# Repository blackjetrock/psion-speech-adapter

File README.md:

# psion-speech-adapter
Psion Organiser speech adatper

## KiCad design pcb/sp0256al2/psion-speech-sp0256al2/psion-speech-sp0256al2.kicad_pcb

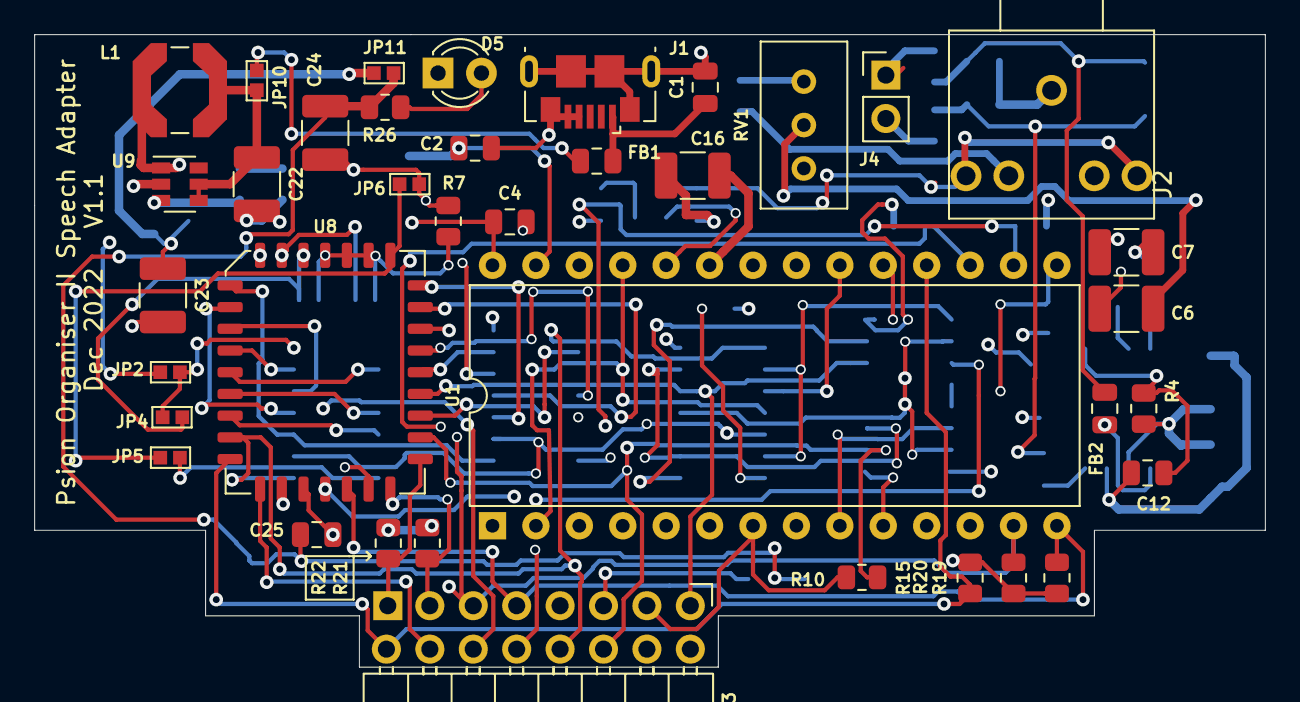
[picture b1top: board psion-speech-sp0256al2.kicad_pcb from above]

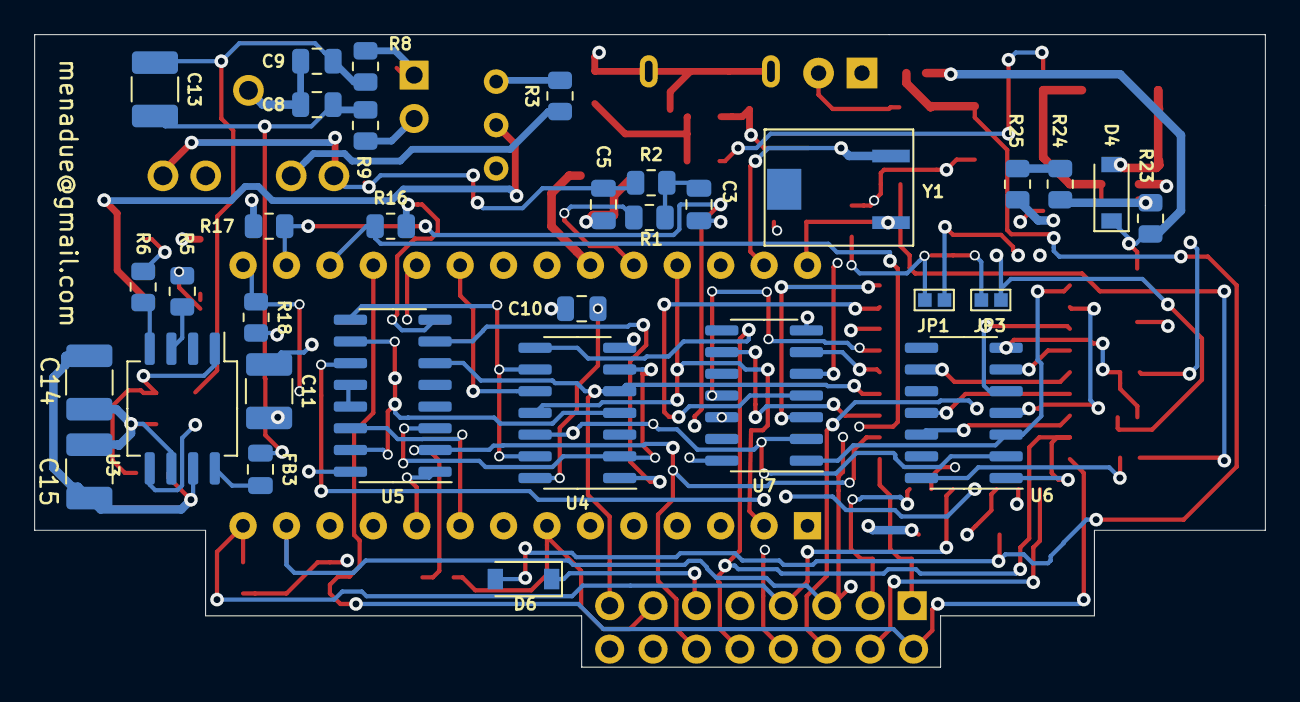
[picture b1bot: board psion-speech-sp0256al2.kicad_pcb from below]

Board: 4 copper layers, 72.0 x 37.0 mm, 71 parts (33 on the bottom side), 68 nets.

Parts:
C1: 10nF; C_0805_2012Metric
C2, C4: 12pF; C_0805_2012Metric
C3, C5: 22nF; C_0805_2012Metric
C6, C7: 1uF; C_1210_3225Metric_Pad1.33x2.70mm_HandSolder
C8, C9: 220pF; C_0805_2012Metric
C10, C12, C25: 100nF; C_0805_2012Metric
C11, C24: 10uF; C_1210_3225Metric_Pad1.33x2.70mm_HandSolder
C13: nopop; C_1210_3225Metric_Pad1.33x2.70mm_HandSolder
C14, C15, C16: 20uF; C_1210_3225Metric_Pad1.33x2.70mm_HandSolder
C22, C23: 22uF; C_1210_3225Metric_Pad1.33x2.70mm_HandSolder
D4, D6: SS36; D_SOD-123
D5: LED; LED_D3.0mm
FB1, FB2, FB3: Laird Technologies Part # MI0805K400R-10; C_0805_2012Metric
J1: Connector_USB_B_Micro; USB_Micro-B_GCT_USB3076-30-A
J2: AudioJack2_Ground_Switch; truconnect_stereo_audio_5_pin
J3: Conn_02x08_Odd_Even; Psion_datapak_2x08_P2.54mm_Horizontal
J4: Conn_01x02_Female; PinHeader_1x02_P2.54mm_Vertical
JP1, JP2, JP3, JP4, JP5, JP6, JP10: Jumper_NO_Small; SolderJumper-2_P1.3mm_Open_Pad0.8x0.8mm
JP11: SolderJumper_2_Open; SolderJumper-2_P1.3mm_Open_Pad0.8x0.8mm
L1: 22uH; L_Coilcraft_LPS5030
R1, R2: 33K; R_0805_2012Metric
R3: 0R; R_0805_2012Metric
R4: 10k; R_0805_2012Metric
R5, R6: 100R; R_0805_2012Metric
R7, R10, R15, R16, R17, R18, R19, R20, R21, R22: 47k; R_0805_2012Metric
R8, R9: R_Small; R_0805_2012Metric
R23: 100k; R_0805_2012Metric
R24: 5k; R_0805_2012Metric
R25: 1k; R_0805_2012Metric
R26: 1k8; R_0805_2012Metric
RV1: 10k; Potentiometer_Bourns_3296W_Vertical
U1: SP0256AL2; DIP-28_W15.24mm
U3: PAM8302AAD; SO-8_5.3x6.2mm_P1.27mm
U4: 4011; SOIC-14_3.9x8.7mm_P1.27mm
U5: 74LS368; SOIC-16_3.9x9.9mm_P1.27mm
U6, U7: 4024; SOIC-14_3.9x8.7mm_P1.27mm
U8: SST39SF020; PLCC-32_11.4x14.0mm_P1.27mm
U9: Regulator_Switching_MT3608; SOT-23-6
Y1: 3.2768MHz; crystal_um4s

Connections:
5VUSB: FB1.1, JP10.1
+10V_PSION: C24.1, C25.1, D6.2, JP11.2, R26.1
A15: JP1.1, JP2.1, U8.3
A16: JP3.1, JP4.1, U8.2
A17: JP5.1, JP6.1, U8.30
ALD: U1.20, U4.10
GND: C1.2, C2.2, C3.2, C4.2, C5.2, C7.2, C8.2, C9.2, C10.2, C11.2, C12.2, C14.2, C15.2, C16.2, C22.2, C23.2, C24.2, C25.2, D5.1, J1.4, J1.5, J1.6, J2.G, J3.9, JP2.2, JP4.2, JP6.2, R7.2, R15.2, R16.2, R17.2, R18.2, R19.2, R20.2, R21.2, R22.2, R25.2, RV1.3, U1.1, U1.10, U1.11, U1.22, U3.7, U4.7, U5.1, U5.8, U6.7, U7.7, U8.16, U9.2
LRQ: U1.9, U5.14
NOT_SEL_SOE_1: U4.9, U4.13, U5.9
N_SOE: U4.1, U5.7
N_SS: U4.2, U4.6, U5.3
unnamed: C1.1, FB1.2, J1.1
unnamed: C2.1, U1.27, Y1.1
unnamed: C3.1, R1.1, R2.2
unnamed: C4.1, U1.28, Y1.2
unnamed: C5.1, J2.S, J2.T, R2.1
unnamed: C6.1, R5.2
unnamed: C6.2, RV1.2
unnamed: C7.1, R6.2
unnamed: C12.1, R4.2, U3.1
unnamed: C9.1, C13.1, FB2.1, R8.2
unnamed: C8.1, C13.2, FB3.1, R9.1
unnamed: C22.1, JP10.2, L1.1, U9.4, U9.5
unnamed: C23.1, D4.1, JP11.1, R23.1
unnamed: D4.2, L1.2, U9.1
unnamed: D5.2, R26.2
unnamed: FB2.2, U3.5
unnamed: FB3.2, U3.8
unnamed: J2.SN, R3.1
unnamed: J4.1, R8.1
unnamed: J4.2, R9.2
unnamed: R1.2, U1.24
unnamed: R3.2, RV1.1
unnamed: R5.1, U3.3
unnamed: R6.1, U3.4
unnamed: R23.2, R24.1, U9.3
unnamed: R24.2, R25.1
unnamed: U5.12, U5.13
unnamed: U6.3, U7.1, U8.5
unnamed: U6.4, U8.6
unnamed: U6.5, U8.7
unnamed: U6.6, U8.8
unnamed: U6.9, U8.9
unnamed: U6.11, U8.10
unnamed: U6.12, U8.11
unnamed: U7.3, U8.29
unnamed: U7.4, U8.28
unnamed: U7.5, U8.4
unnamed: U7.6, U8.25
unnamed: U7.9, U8.23
unnamed: U7.11, U8.26
unnamed: U7.12, U8.27
RST: U1.2, U1.25, U4.11
SCLK: J3.10, U4.8, U6.1, U8.12
SD0: J3.2, R15.1, U1.18, U8.13
SD1: J3.4, R16.1, U1.17, U8.14
SD2: J3.6, R17.1, U1.16, U8.15
SD3: J3.8, R18.1, U1.15, U8.17
SD4: J3.7, R19.1, U1.14, U8.18
SD5: J3.5, R20.1, U1.13, U8.19
SD6: J3.3, R21.1, U8.20
SD7: J3.1, R22.1, U5.11, U8.21
SEL_SOE_1: U4.4, U5.10, U5.15
SMR: J3.16, U4.12, U6.2, U7.2
SOE: J3.15, U4.5, U5.6, U8.24
SS: J3.12, R10.2, U5.2, U8.22
SVCC: C10.1, C11.1, C14.1, C15.1, C16.1, J3.13, JP1.2, JP3.2, JP5.2, R4.1, R7.1, R10.1, U1.7, U1.19, U1.23, U3.6, U4.14, U5.16, U6.14, U7.14, U8.1, U8.31, U8.32
VB: D6.1, J3.11
